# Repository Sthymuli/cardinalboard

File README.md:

# Cardinalboard
smaller board that goes with [the motherboard](https://github.com/Sthymuli/motherboard)

## 3D view

| Top | Bottom |
|---|---|
|  |  |

## Exports

Regenerated automatically by the [export workflow](.github/workflows/export.yml) on every push to `main` that changes the design:

* [Schematic (PDF)](exports/Sthymuli-cardinalboard_schematic.pdf)
* [Layout (PDF, one page per layer)](exports/Sthymuli-cardinalboard_layout.pdf)
* 3D models (STEP), one per board as they are after breaking the mouse-bite tabs, for fit checks in the enclosure CAD:
  * [main board](exports/Sthymuli-cardinalboard.step)
  * [sensor board](exports/Sthymuli-cardinalboard_sensor.step) (mounts at 90° on J2)
* [3D render, top](exports/Sthymuli-cardinalboard_3d_top.png) / [bottom](exports/Sthymuli-cardinalboard_3d_bottom.png)

To run the same export locally: `scripts/export.sh` (see the comment at the top of the script for the Flatpak KiCad variant).

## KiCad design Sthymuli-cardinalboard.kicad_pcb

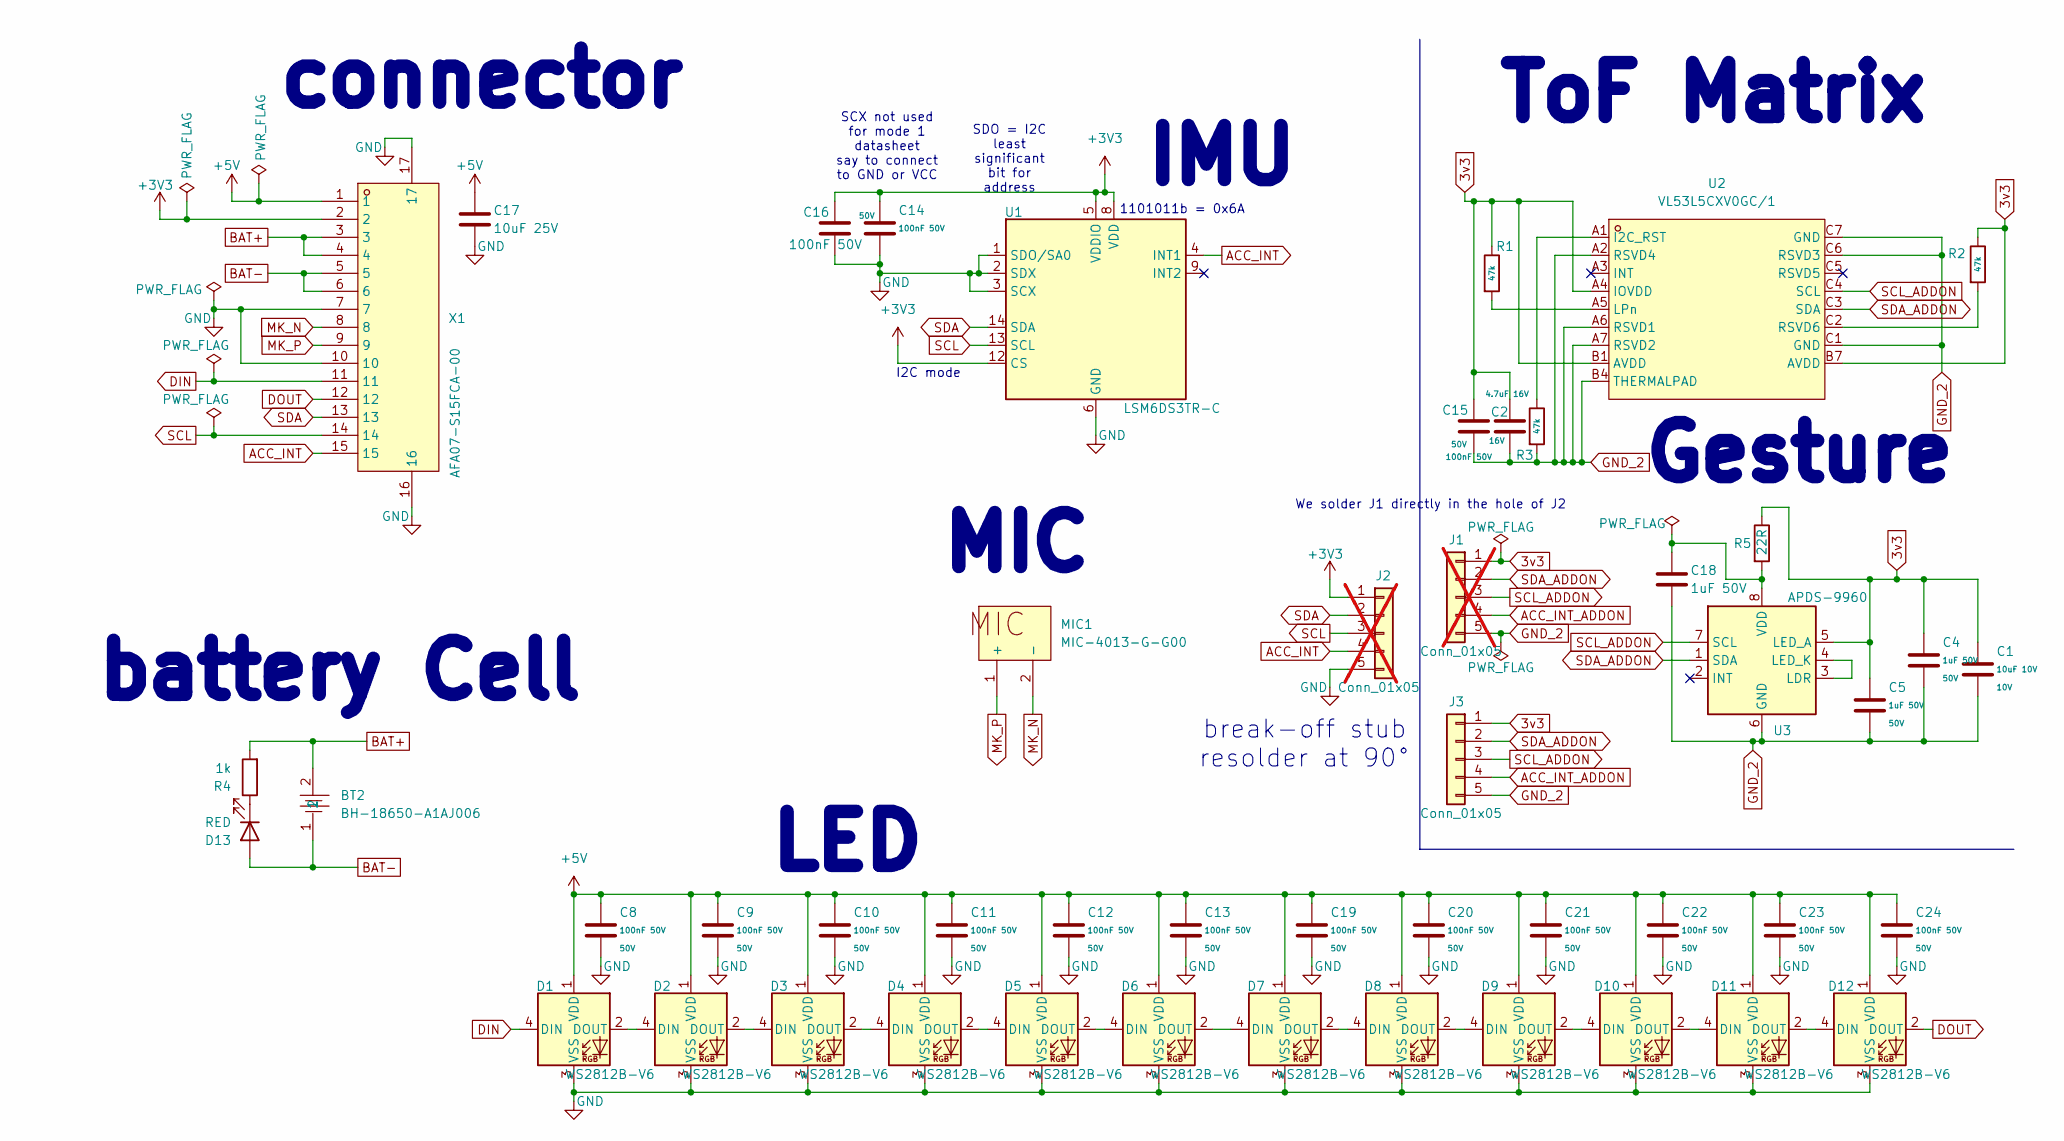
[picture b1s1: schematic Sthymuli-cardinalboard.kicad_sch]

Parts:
BT2: BH-18650-A1AJ006; BAT-TH_BH-18650-A1AJ006; MPN BH-18650-A1AJ006; LCSC Part C5290175
C1: 10uF 10V; C_0603_1608Metric; Voltage Rated 10V; Tolerance ±10%; Part CL10A106KP8NNNC; LCSC C19702
C2: 4.7uF 16V; C_0603_1608Metric; Voltage Rated 16V; Tolerance ±10%; Part CL10A475KO8NNNC; LCSC C19666
C4, C5: 1uF 50V; C_0603_1608Metric; Voltage Rated 50V; Tolerance ±10%; Part CL10A105KB8NNNC; LCSC C15849
C8, C9, C10, C11, C12, C13, C14, C15, C19, C20, C21, C22, C23, C24: 100nF 50V; C_0603_1608Metric; Voltage Rated 50V; Tolerance ±10%; Part CC0603KRX7R9BB104; LCSC C14663
C16: 100nF 50V; C_0603_1608Metric; LCSC C14663
C17: 10uF 25V; C_0805_2012Metric; LCSC C15850
C18: 1uF 50V; C_0603_1608Metric; LCSC C15849
D1, D2, D3, D4, D5, D6, D7, D8, D9, D10, D11, D12: WS2812B-V6; LED_WS2812B_PLCC4_5.0x5.0mm_P3.2mm; LCSC C52917433
D13: RED; LED_0603_1608Metric; LCSC C2286
J1: Conn_01x05; HDR-SMD_5P-P2.54-H-M-W13.3-N; LCSC C5242198; not fitted
J2: Conn_01x05; PinHeader_1x05_P2.54mm_Vertical; not fitted
J3: Conn_01x05; HDR-SMD_5P-P2.54-H-M-W13.3-N; LCSC C5242198
MIC1: MIC-4013-G-G00; MIC-SMD_BD4.0-4013_SMDA; MPN MIC-4013-G-G00; LCSC Part C42371093
R1, R2, R3: 47k; R_0603_1608Metric; Overload Voltage (Max) 75V; Tolerance ±1%; Part 0603WAF4702T5E; LCSC C25819
R4: 1k; R_0603_1608Metric; LCSC C21190
R5: 22R; R_0603_1608Metric; LCSC C23345
U1: LSM6DS3TR-C; LGA-14_3x2.5mm_P0.5mm_LayoutBorder3x4y; LCSC C967633
U2: VL53L5CXV0GC/1; LGA-16_L6.4-W3.0_VL53L5CXV0GC-1; MPN VL53L5CXV0GC/1; LCSC Part C3178303
U3: APDS-9960; Avago_APDS-9960; LCSC C93222
X1: AFA07-S15FCA-00; FPC-SMD_15P-P1.00_JS_AFA07-S15XXX; MPN AFA07-S15FCA-00; LCSC Part C262721

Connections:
3v3: C1.1, C2.1, C4.1, C5.1, C15.1, J1.1, J3.1, R1.1, R2.1, R5.1, U2.A4 (IOVDD), U2.B1 (AVDD), U2.B7 (AVDD), U3.5 (LED_A)
+3V3: C14.1, C16.1, J2.1, U1.5 (VDDIO), U1.8 (VDD), U1.12 (CS), X1.2
+5V: C8.1, C9.1, C10.1, C11.1, C12.1, C13.1, C17.1, C19.1, C20.1, C21.1, C22.1, C23.1, C24.1, D1.1 (VDD), D2.1 (VDD), D3.1 (VDD), D4.1 (VDD), D5.1 (VDD), D6.1 (VDD), D7.1 (VDD), D8.1 (VDD), D9.1 (VDD), D10.1 (VDD), D11.1 (VDD), D12.1 (VDD), X1.1
ACC_INT: J2.4, U1.4 (INT1), X1.15
ACC_INT_ADDON: J1.4, J3.4
BAT+: BT2.2, R4.2, X1.3, X1.4
BAT-: BT2.1, D13.2 (A), X1.5, X1.6
DIN: D1.4 (DIN), X1.11
DOUT: D12.2 (DOUT), X1.12
GND: C8.2, C9.2, C10.2, C11.2, C12.2, C13.2, C14.2, C16.2, C17.2, C19.2, C20.2, C21.2, C22.2, C23.2, C24.2, D1.3 (VSS), D2.3 (VSS), D3.3 (VSS), D4.3 (VSS), D5.3 (VSS), D6.3 (VSS), D7.3 (VSS), D8.3 (VSS), D9.3 (VSS), D10.3 (VSS), D11.3 (VSS), D12.3 (VSS), J2.5, U1.1 (SDO/SA0), U1.2 (SDX), U1.3 (SCX), U1.6 (GND), U1.7 (GND), X1.7, X1.10, X1.16, X1.17
GND_2: C1.2, C2.2, C4.2, C5.2, C15.2, C18.2, J1.5, J3.5, R3.2, U2.A2 (RSVD4), U2.A6 (RSVD1), U2.A7 (RSVD2), U2.B4 (THERMALPAD), U2.C1 (GND), U2.C6 (RSVD3), U2.C7 (GND), U3.6 (GND)
MK_N: MIC1.2 (-), X1.8
MK_P: MIC1.1 (+), X1.9
unnamed: D1.2 (DOUT), D2.4 (DIN)
unnamed: D2.2 (DOUT), D3.4 (DIN)
unnamed: D3.2 (DOUT), D4.4 (DIN)
unnamed: D4.2 (DOUT), D5.4 (DIN)
unnamed: D5.2 (DOUT), D6.4 (DIN)
unnamed: D6.2 (DOUT), D7.4 (DIN)
unnamed: D7.2 (DOUT), D8.4 (DIN)
unnamed: D8.2 (DOUT), D9.4 (DIN)
unnamed: D9.2 (DOUT), D10.4 (DIN)
unnamed: D10.2 (DOUT), D11.4 (DIN)
unnamed: D11.2 (DOUT), D12.4 (DIN)
unnamed: D13.1 (K), R4.1
unnamed: R3.1, U2.A1 (I2C_RST)
unnamed: R1.2, U2.A5 (LPn)
unnamed: R2.2, U2.C2 (RSVD6)
unnamed: U3.3 (LDR), U3.4 (LED_K)
unnamed: C18.1, R5.2, U3.8 (VDD)
SCL: J2.3, U1.13 (SCL), X1.14
SCL_ADDON: J1.3, J3.3, U2.C4 (SCL), U3.7 (SCL)
SDA: J2.2, U1.14 (SDA), X1.13
SDA_ADDON: J1.2, J3.2, U2.C3 (SDA), U3.1 (SDA)

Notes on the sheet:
Gesture
SCX not used for mode 1 datasheet say to connect to GND or VCC
IMU
We solder J1 directly in the hole of J2
1101011b = 0x6A
SDO = I2C least significant bit for address
I2C mode
battery Cell
ToF Matrix
MIC
connector
LED
break-off stub resolder at 90°

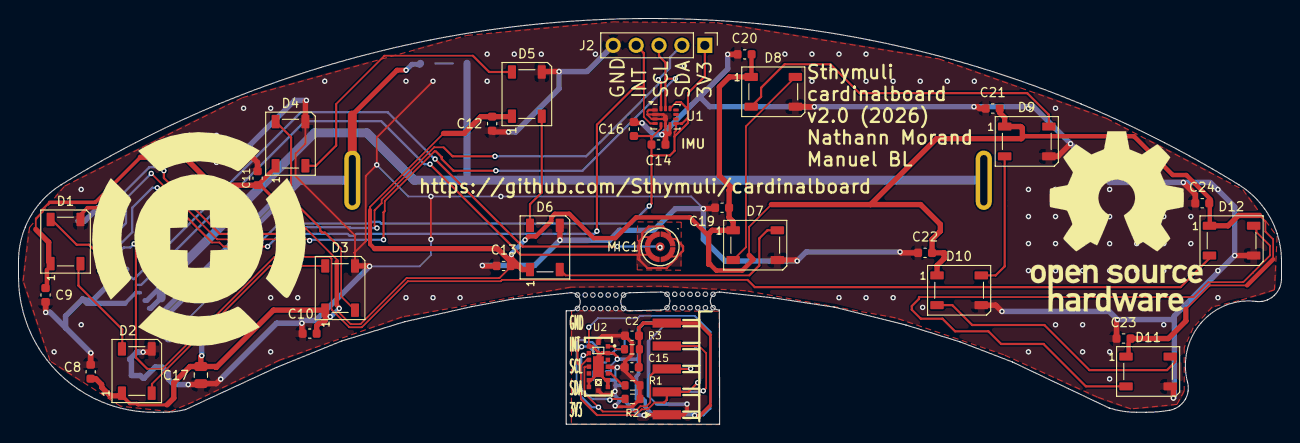
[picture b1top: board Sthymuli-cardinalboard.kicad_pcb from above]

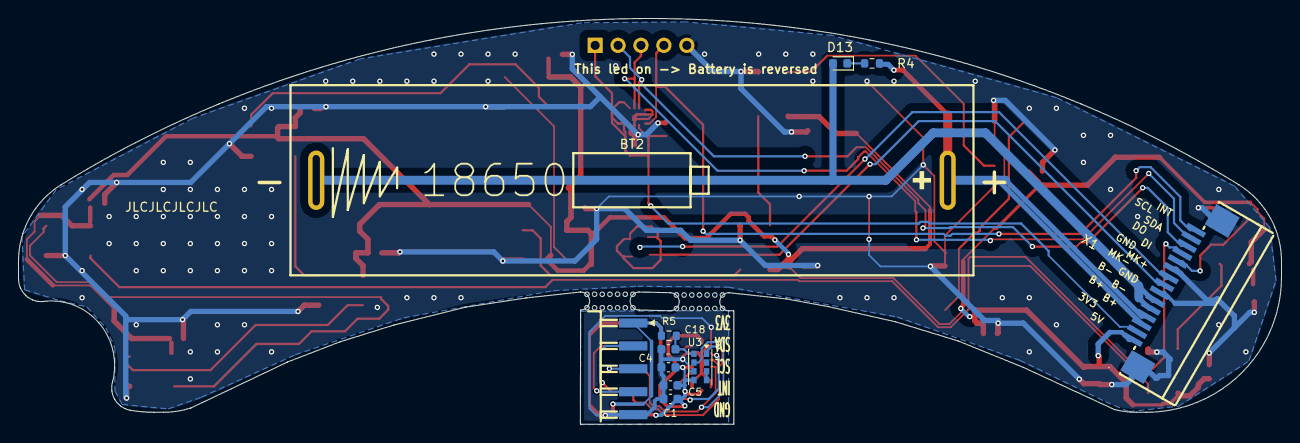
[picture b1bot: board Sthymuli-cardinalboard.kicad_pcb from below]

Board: 2 copper layers, 140.0 x 45.0 mm, 48 parts (11 on the bottom side), 34 nets.
